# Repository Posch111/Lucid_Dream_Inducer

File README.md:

# REM Sleep Cycle Monitor
EOG Sleep cycle monitor project
---
Installing Kicad and set up libraries
---
Windows/Mac
* Download KiCAD from [the KiCAD website](http://kicad-pcb.org/download/) to download KiCAD 5+ and 6+ when 6 is released.
* Follow installation wizards, and install KiCAD.
* Through the terminal, clone the repository into a git folder with the 'git clone <URL>' command when you are in the desired folder.
**Mac user NOTE:** if you get this error 
  
  `xcrun: error: invalid active developer path
 (/Library/Developer/CommandLineTools), missing xcrun at:
 /Library/Developer/CommandLineTools/usr/bin/xcrun`
 use this command in the terminal: `xcode-select --install`
* In KiCAD, go to File > Open Project and navigate to the /<git directory>/REM_Sleep_Cycle_Monitor/Hardware/KICAD/REM_sleep_analysis.pro to click "Open"
* Open the schematic editor and click the second option which says "Import from file" with the file "sim-lib-table" in the same folder as the project file.
* In the schematic editor, go to Preferences > Manage Symbol Libraries...
* Change to the "Project Specific Libraries" tab

Ubuntu
* Add ppa through terminal with these commands:

       sudo add-apt-repository --yes ppa:js-reynaud/kicad-5
       sudo apt update
       sudo apt install kicad

* Through the terminal, clone the repository into a git folder with the 'git clone <URL>' command when you are in the desired folder.
* In KiCAD, go to File > Open Project and navigate to the /<git directory>/REM_Sleep_Cycle_Monitor/Hardware/KICAD/REM_sleep_analysis.pro to click "Open"
  
Arch Linux

      sudo pacman -S kicad 

* Through the terminal, clone the repository into a git folder with the 'git clone <URL>' command when you are in the desired folder.
* In KiCAD, go to File > Open Project and navigate to the /<git directory>/REM_Sleep_Cycle_Monitor/Hardware/KICAD/REM_sleep_analysis.pro to click "Open"

---
Installing Android Studio
---
https://developer.android.com/studio/

---
Soldering and Testing Device
---
TODO

---
Bluetooth Operations
---
TODO

----
Bluetooth Command List
----
TODO

<!-- Target:  GitHub Flavor Markdown.  To test locally:  pandoc -f markdown_github -t html README.md  -->

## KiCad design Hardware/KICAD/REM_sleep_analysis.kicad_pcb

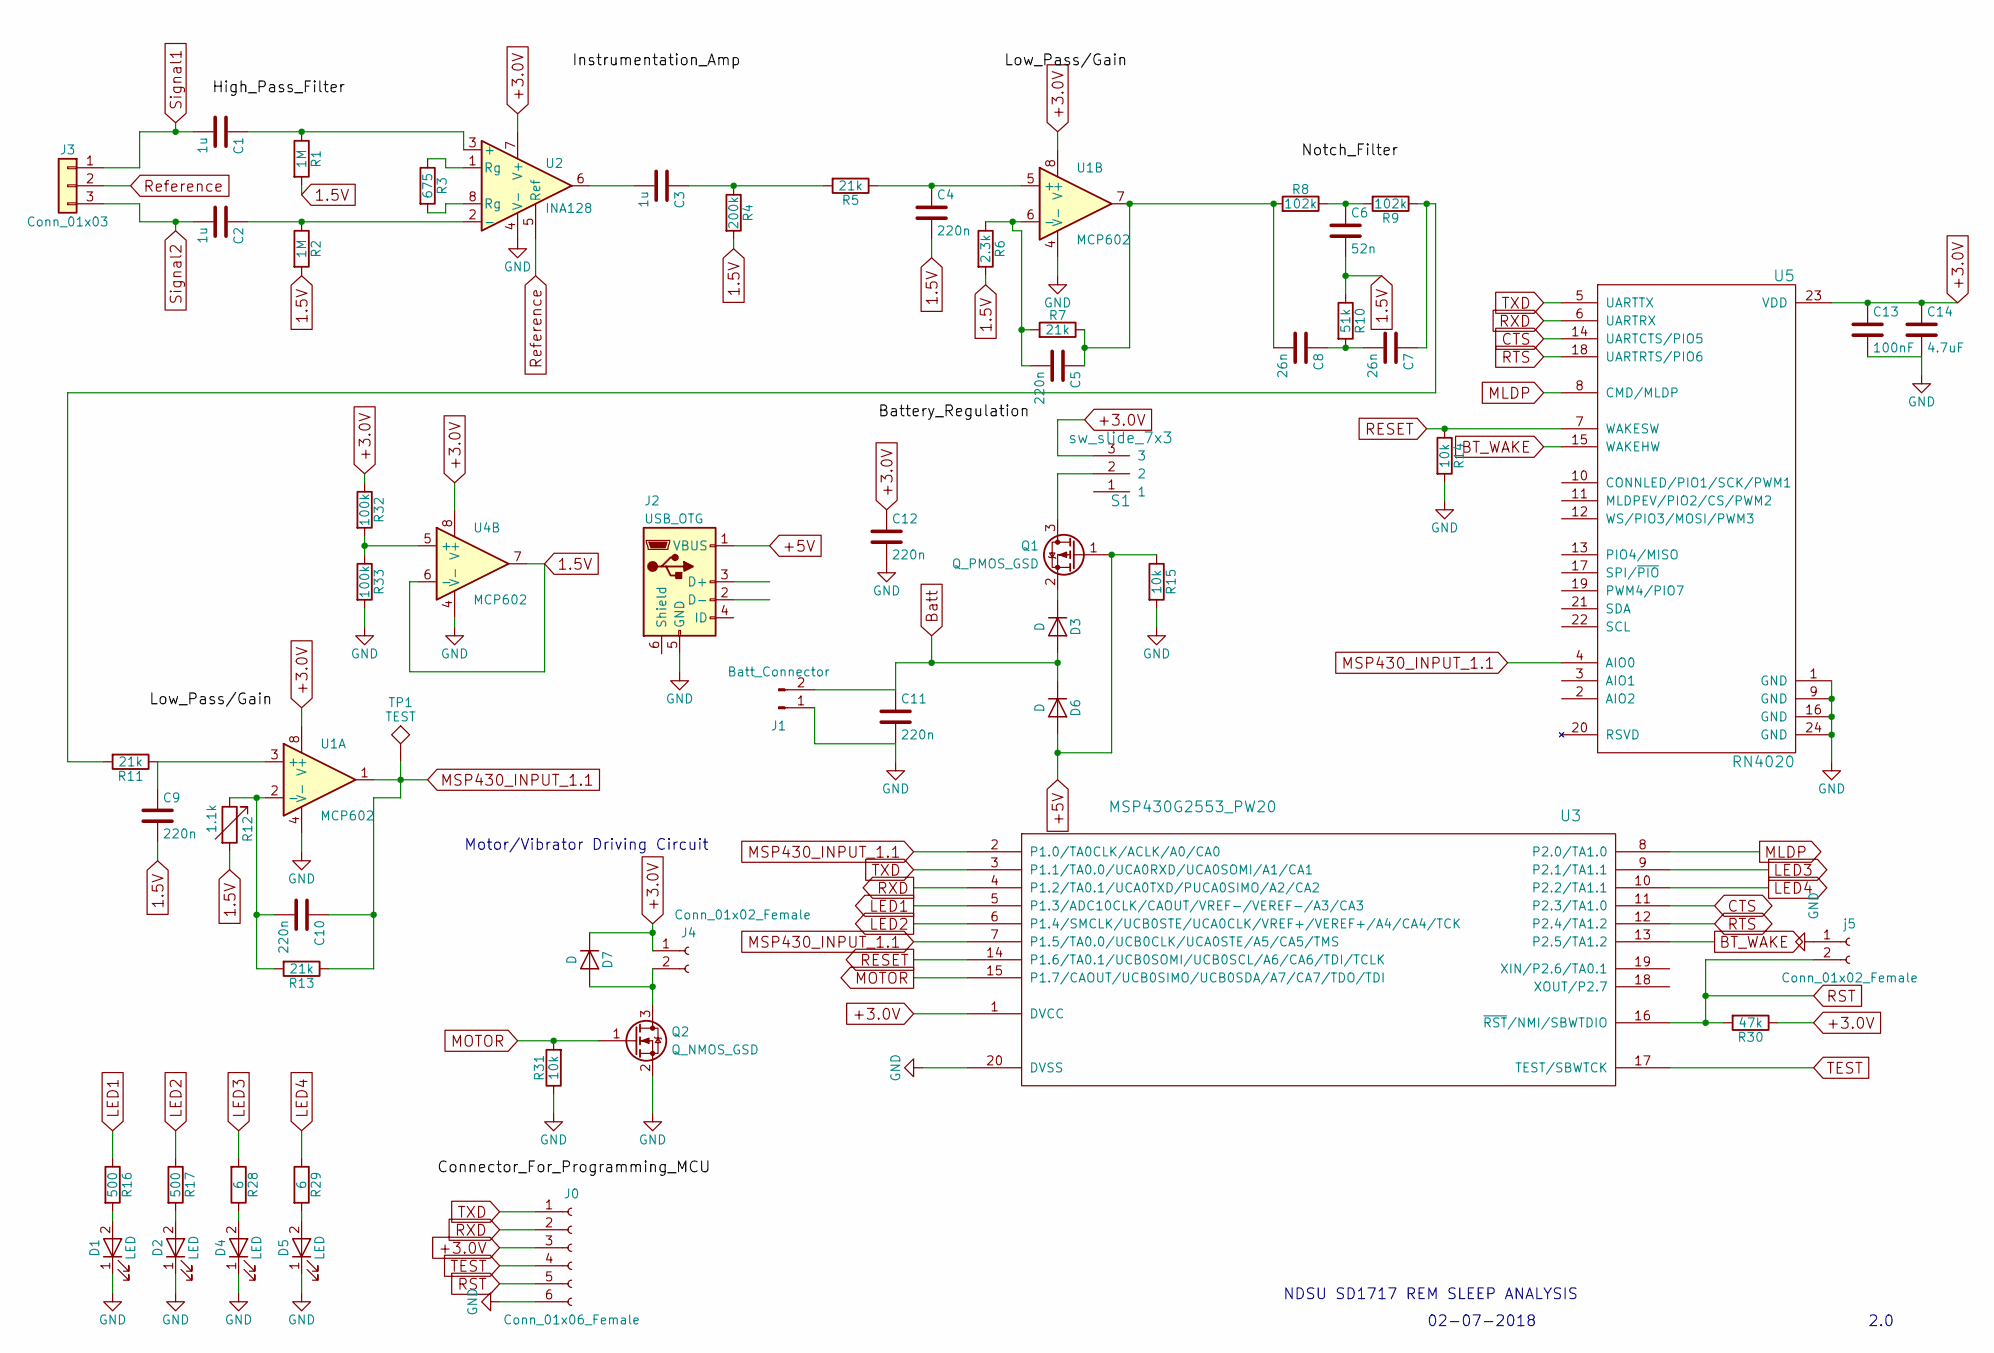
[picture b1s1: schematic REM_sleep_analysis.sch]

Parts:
C1, C2, C3: 1u; C_0603_1608Metric
C4, C5, C9, C10, C11, C12: 220n; C_0603_1608Metric
C6: 52n; C_0603_1608Metric
C7, C8: 26n; C_0603_1608Metric
C13: 100nF; C_0603_1608Metric
C14: 4.7uF; C_0603_1608Metric
D1: LED; LED_1206_3216Metric; PartNumber 511-1272-1-ND
D2: LED; LED_1206_3216Metric; PartNumber 511-1274-1-ND
D3, D6, D7: D; D_0603_1608Metric
D4, D5: LED; LED_D3.0mm; PartNumber C503B-RCN-CW0Z0AA1-ND
J0: Conn_01x06_Female; PinSocket_1x06_P2.54mm_Vertical
J1: Batt_Connector; PinHeader_1x02_P2.54mm_Horizontal
J2: USB_OTG; USB_Micro-B_Molex_47346-0001
J3: Conn_01x03; PinHeader_1x03_P2.54mm_Horizontal
J4: Conn_01x02_Female; PinHeader_1x02_P2.54mm_Vertical
Q1: Q_PMOS_GSD; SOT-23
Q2: Q_NMOS_GSD; SOT-723
R1, R2: 1M; R_0603_1608Metric
R3: 675; R_0603_1608Metric
R4: 200k; R_0603_1608Metric
R5, R7, R11, R13: 21k; R_0603_1608Metric
R6: 2.3k; R_0603_1608Metric
R8, R9: 102k; R_0603_1608Metric
R10: 51k; R_0603_1608Metric
R12: 1.1k; R_0603_1608Metric
R14, R15, R31: 10k; R_0603_1608Metric
R16, R17: 500; R_0603_1608Metric
R28, R29: 6; R_0603_1608Metric
R30: 47k; R_0603_1608Metric
R32, R33: 100k; R_0603_1608Metric
S1: sw_slide_7x3
TP1: TEST; PinSocket_1x01_P2.54mm_Vertical
U1, U4: MCP602; SOIC-8_3.9x4.9mm_P1.27mm
U2: INA128; SOIC-8_3.9x4.9mm_P1.27mm
U3: MSP430G2553_PW20; TSSOP-20_4.4x6.5mm_P0.65mm
U5: RN4020
j5: Conn_01x02_Female; R_0603_1608Metric

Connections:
1.5V: C4.2, C6.2, C9.2, R1.2, R2.2, R4.2, R6.2, R10.1, R12.2, U4.6 (-), U4.7
+3.0V: C12.1, C13.1, C14.1, D7.1 (K), J0.3, J4.1, R30.1, R32.1, S1.3, U1.8 (V+), U2.7 (V+), U3.1 (DVCC), U4.8 (V+), U5.23 (VDD)
+5V: D6.2 (A), J2.1 (VBUS), Q1.1 (G), R15.1
BT_WAKE: U3.13 (P2.5/TA1.2), U5.15 (WAKEHW)
Batt: C11.1, D3.2 (A), D6.1 (K), J1.2
CTS: U3.11 (P2.3/TA1.0), U5.14 (UARTCTS/PIO5)
GND: C11.2, C12.2, C13.2, C14.2, D1.1 (K), D2.1 (K), D4.1 (K), D5.1 (K), J0.6, J1.1, J2.5 (GND), Q2.2 (S), R14.2, R15.2, R31.1, R33.2, U1.4 (V-), U2.4 (V-), U3.20 (DVSS), U4.4 (V-), U5.1 (GND), U5.9 (GND), U5.16 (GND), U5.24 (GND), j5.1
LED1: R16.1, U3.5 (P1.3/ADC10CLK/CAOUT/VREF-/VEREF-/A3/CA3)
LED2: R17.1, U3.6 (P1.4/SMCLK/UCB0STE/UCA0CLK/VREF+/VEREF+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)
LED3: R28.2, U3.9 (P2.1/TA1.1)
LED4: R29.1, U3.10 (P2.2/TA1.1)
MLDP: U3.8 (P2.0/TA1.0), U5.8 (CMD/MLDP)
MOTOR: Q2.1 (G), R31.2, U3.15 (P1.7/CAOUT/UCB0SIMO/UCB0SDA/A7/CA7/TDO/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)
MSP430_INPUT_1.1: C10.1, R13.1, TP1.1, U1.1, U3.2 (P1.0/TA0CLK/ACLK/A0/CA0), U3.7 (P1.5/TA0.0/UCB0CLK/UCA0STE/A5/CA5/TMS), U5.4 (AIO0)
unnamed: C1.1, R1.1, U2.3 (+)
unnamed: C2.1, R2.1, U2.2 (-)
unnamed: C3.1, R4.1, R5.2
unnamed: C3.2, U2.6
unnamed: C4.1, R5.1, U1.5 (+)
unnamed: C5.1, C8.2, R7.1, R8.2, U1.7
unnamed: C5.2, R6.1, R7.2, U1.6 (-)
unnamed: C6.1, R8.1, R9.2
unnamed: C7.1, R9.1, R11.2
unnamed: C7.2, C8.1, R10.2
unnamed: C9.1, R11.1, U1.3 (+)
unnamed: C10.2, R12.1, R13.2, U1.2 (-)
unnamed: D1.2 (A), R16.2
unnamed: D2.2 (A), R17.2
unnamed: D3.1 (K), Q1.2 (S)
unnamed: D4.2 (A), R28.1
unnamed: D5.2 (A), R29.2
unnamed: D7.2 (A), J4.2, Q2.3 (D)
unnamed: Q1.3 (D), S1.2
unnamed: R3.1, U2.1 (Rg)
unnamed: R3.2, U2.8 (Rg)
unnamed: R32.2, R33.1, U4.5 (+)
RESET: R14.1, U3.14 (P1.6/TA0.1/UCB0SOMI/UCB0SCL/A6/CA6/TDI/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), U5.7 (WAKESW)
RST: J0.5, R30.2, U3.16 (~RST~/NMI/SBWTDIO), j5.2
RTS: U3.12 (P2.4/TA1.2), U5.18 (UARTRTS/PIO6)
RXD: J0.2, U3.4 (P1.2/TA0.1/UCA0TXD/PUCA0SIMO/A2/CA2), U5.6 (UARTRX)
Reference: J3.2, U2.5 (Ref)
Signal1: C1.2, J3.1
Signal2: C2.2, J3.3
TEST: J0.4, U3.17 (TEST/SBWTCK)
TXD: J0.1, U3.3 (P1.1/TA0.0/UCA0RXD/UCA0SOMI/A1/CA1), U5.5 (UARTTX)

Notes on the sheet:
Motor/Vibrator Driving Circuit
2.0
02-07-2018
NDSU SD1717 REM SLEEP ANALYSIS

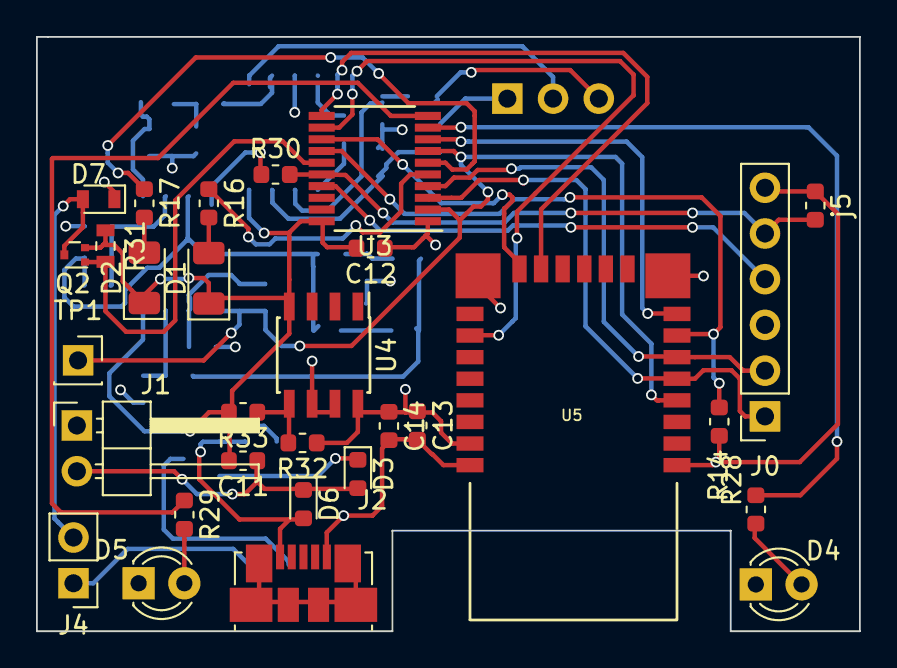
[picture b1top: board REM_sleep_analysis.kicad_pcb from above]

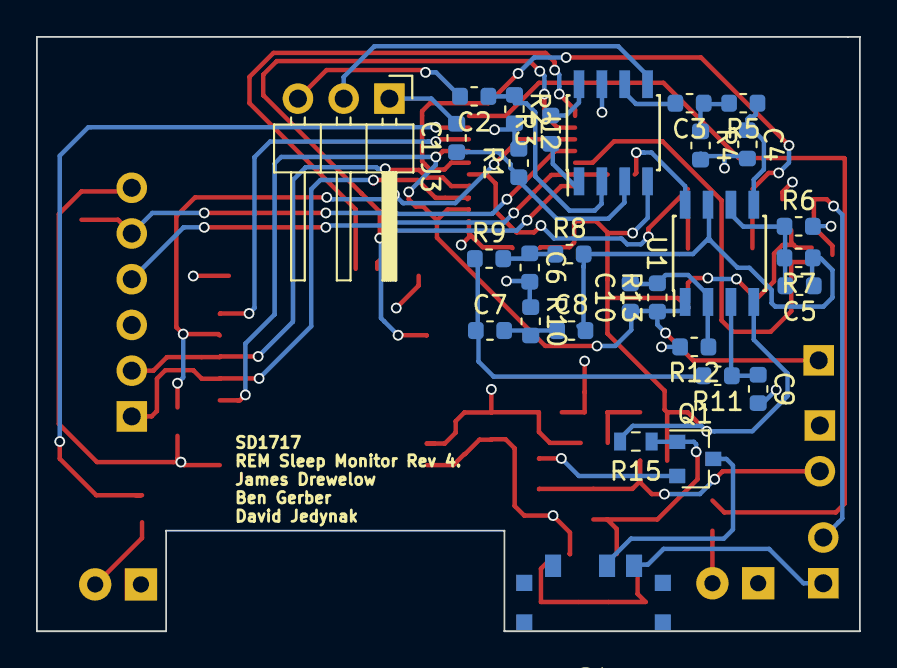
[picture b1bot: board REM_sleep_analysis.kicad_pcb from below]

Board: 4 copper layers, 45.7 x 33.0 mm, 59 parts (29 on the bottom side), 45 nets.

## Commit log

2019-01-29 Create new repository
2019-02-27 update lucidio
2019-02-27 sync
2019-02-28 ble work
2019-03-13 Bluetooth Connecting
    Many small changes, removing excess code, primarily making bluetooth connection more reliable.
2019-04-05 latest
2019-04-11 Data transfer and graphing in sleep mode
2019-04-13 embedded code
2019-04-15 Update
    everything
2019-04-15 readme
2019-04-16 timer interrupts
2019-04-16 Stable
2019-04-16 bugs fix
2019-04-16 LED starting at 3am
2019-04-16 generic file writing
2019-04-17 Data saving capabilities
    works on any phone,
    prevents large memory usage,
    graph improved.
2019-04-17 fixed LED setting bug
2019-04-17 factory reset working
2019-04-17 Buffer size increase
2019-04-17 Settings change and sleep button bug fix
2019-04-24 protocol timer bug fix
2019-04-25 bug fixes
    small bug with protocol and Set name changed to SN command.
2019-09-04 offset
    fixed offset
